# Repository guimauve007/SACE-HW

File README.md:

# SACE-HW
Répertoire contenant 2 cartes pour machine SACE:

## Getting started
- Installer la dernière version de KiCad ici: https://www.kicad.org/download/
- Cloner ce répertoire sur votre ordinateur local:

```
git clone https://github.com/guimauve007/SACE-HW.git
```

## carte_controle (V1)
Module de contrôle versatile avec les fonctionnalités suivantes:
- 2 connecteurs BNC pour lecture de tension & de courant des électrodes (à l'oscilloscope)
- 8 GPIO/ADC 12 bits 5V
- 2 sorties 0-5V analog (DAC)
- 2 sorties 0-10V analog (DAC)
- 8 sorties 5V haute vitesse (pour stepper drive)
- 2 relais NO 125VAC-10Amp
- 4 Mosfet Open Drain pour load 12V 5.7Amp Max
- Lecture de tension + courant des électrodes jusqu'à 200kSPS avec résolution 12 bits
- Possibilité d'enregistrer un log de données via carte SD
- Interface web utilisateur avec communication MQTT via ESP32
- Connecteurs I2C (x2) pour accessoires auxiliaires  

## interface_piezzos (V1)
- Amplificateur de signal via OP-Amp en mode comparateur (sortie 0-5V)

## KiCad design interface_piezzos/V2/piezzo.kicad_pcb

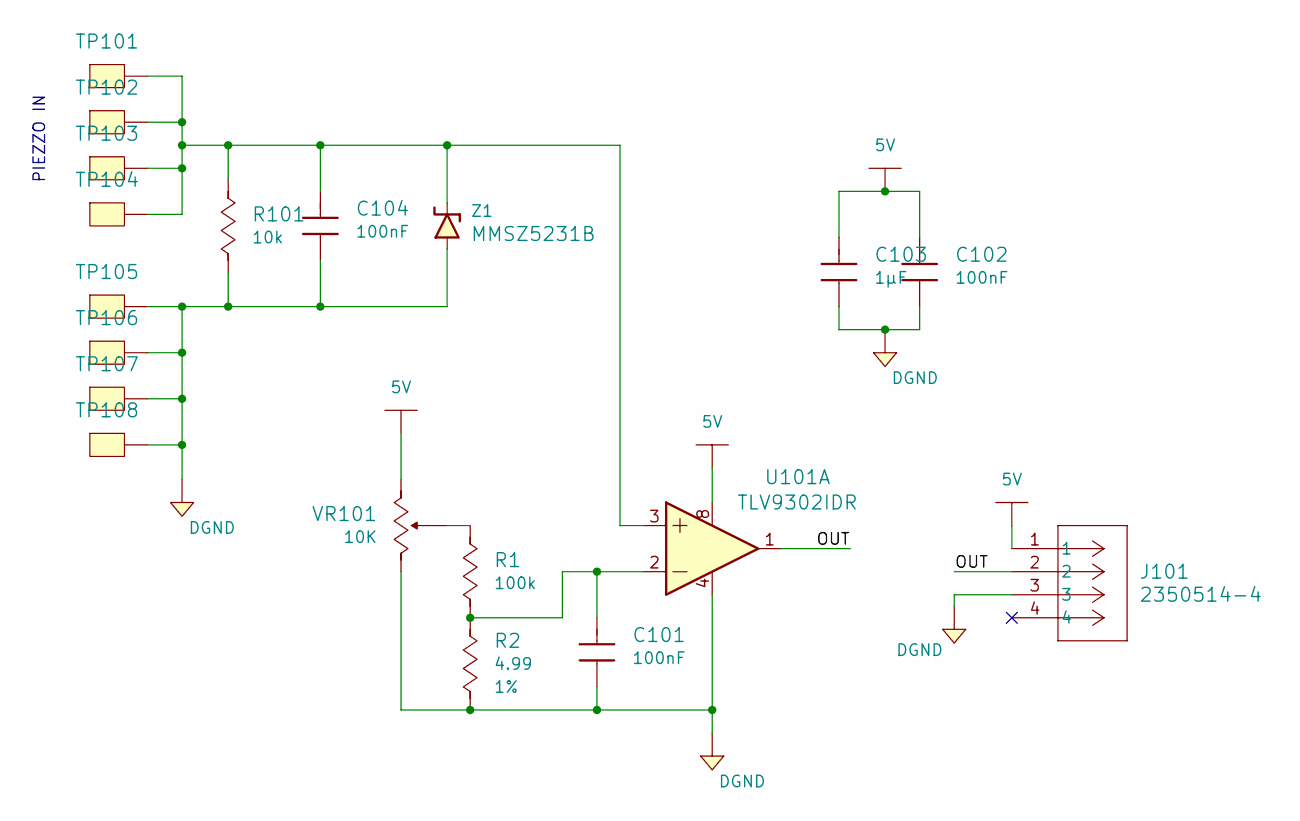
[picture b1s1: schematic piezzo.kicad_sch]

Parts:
C101, C102, C104: 885012207098; C0805; Tolerance (%) ±10%; Voltage Rated (Volt) 50V; Manufacturer Part Number 885012207098
C103: 885012107015; C0805; Tolerance (%) ±20%; Voltage Rated (Volt) 25V; Manufacturer Part Number 885012107015
J101: 2350514-4; CONN4_1155650000_TEC; Manufacturer Part Number 2350514-4
R1: RC0805FR-07100KL; R0805; Tolerance (%) ±1%; Manufacturer Part Number RC0805FR-07100KL
R2: RMCF0805FT4R99; R0805; Tolerance (%) 1%; Manufacturer Part Number RMCF0805FT4R99
R101: RC0805JR-0710KL; R0805; Tolerance (%) ±5%; Manufacturer Part Number RC0805JR-0710KL
TP101, TP102, TP103, TP104, TP105, TP106, TP107, TP108: Test_Point_THM; Keystone_5001; Manufacturer Part Number 5001
U101: TLV9302IDR; IC8_TLV9302IDR_TEX; Manufacturer Part Number TLV9302IDR
VR101: 67WR10KLF; 67W; Tolerance (%) ±10%; Manufacturer Part Number 67WR10KLF
Z1: MMSZ5231B; SOD-123FL; Manufacturer Part Number MMSZ5231B-7-F

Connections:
5V: C102.2, C103.2, J101.1, U101.8, VR101.3
/OUT: J101.2, U101.1
DGND: C101.1, C102.1, C103.1, C104.1, J101.3, R2.1, R101.1, TP105.1 (TP), TP106.1 (TP), TP107.1 (TP), TP108.1 (TP), U101.4, VR101.1, Z1.2 (Anode)
unnamed: C101.2, R1.1, R2.2, U101.2
unnamed: R1.2, VR101.2
unnamed: C104.2, R101.2, TP101.1 (TP), TP102.1 (TP), TP103.1 (TP), TP104.1 (TP), U101.3, Z1.1 (Cathode)

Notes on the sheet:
PIEZZO IN

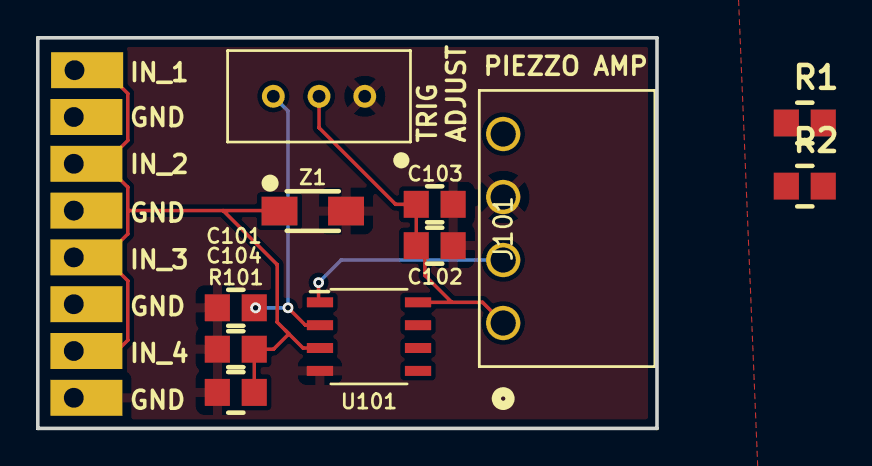
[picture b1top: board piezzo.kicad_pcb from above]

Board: 2 copper layers, 34.4 x 21.7 mm, 19 parts (0 on the bottom side), 6 nets.

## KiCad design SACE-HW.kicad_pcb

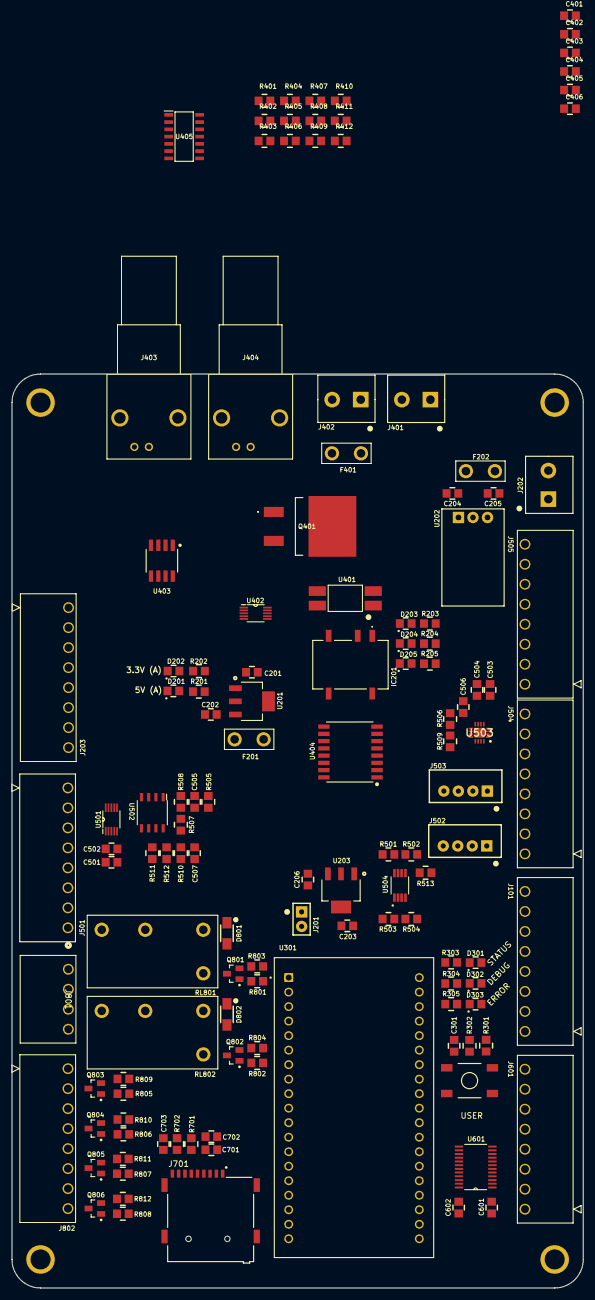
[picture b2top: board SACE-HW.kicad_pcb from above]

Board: 2 copper layers, 100.0 x 160.0 mm, 133 parts (0 on the bottom side), 115 nets, no tracks yet.

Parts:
C201, C203: 885012107005; C0805
C202, C206: 885012107014; C0805
C204, C205: 885012107018; C0805
C301, C401, C403, C405, C601, C602, C702, C703: 885012207098; C0805
C402, C404, C406: 885012207103; C0805
C501, C502, C503, C504, C505, C506, C507, C701: 885012107015; C0805
D201, D202, D203, D204, D205, D301: 150080VS75000; LED_0805_GREEN
D302: 150080YS75000; LED_0805_YELLOW
D303: 150080RS75000; LED_0805_RED
D801, D802: DSS16U; SOD-123FL
F201, F202: 39511000440; TE5_395
F401: 0698Q6300-01; TE5_395
H101, H102, H103, H104: Mounting-Hole-M3; Mounting_Hole_3mm
IC201: 1769205241
J101, J203, J501, J504, J505, J601, J802: 2350514-8; CONN8_2350514-8_TEC
J201: Header_Male_Pin_2.54mm_1X2_,_Unshrouded; Headers_2.54mm_1X2
J202, J401, J402: 1935161
J403, J404: RF1-01K-D-00-50-BK-HDW; RF101KD0050
J502, J503: XH-4A connector; XH-4A
J701: MEM2075-00-140-01-A; GCT_MEM2075-00-140-01-A
J801: 2350514-4; CONN4_1155650000_TEC
Q401: MCB90N12A-TP; MCB90N12ATP
Q801, Q802, Q803, Q804, Q805, Q806: PMV20XNER; SOT-23-3
R201, R204, R404: RC0805FR-075K6L; R0805
R202, R205, R303, R304, R305, R403, R505, R510: RC0805JR-072K2L; R0805
R203: RC0805JR-0733KL; R0805
R301, R501, R502, R503, R504: RC0805JR-074K7L; R0805
R302, R702: RC0805JR-07150RL; R0805
R401, R406, R407, R409, R411, R507, R508, R511, R512, R513, R803, R804, R809, R810, R811, R812: RC0805JR-0710KL; R0805
R402, R801, R802, R805, R806, R807, R808: RC0805JR-07330RL; R0805
R405, R410: ERJ-6ENF1404V; R0805
R408, R412, R701: RC0805FR-0747KL; R0805
R506, R509: 0hms_0.5W; R0805
RL801, RL802: ALQ312
SW301: PTS645SM43SMTR92; PTS645_6X6X4_SMD
U201, U203: AZ1117IH-3.3TRG1; SOT-223-3
U202: OKI-78SR-5_1.5-W36H-C; OKI-78SR_Horizontal
U301: ESP32-DEVKITC-32D; MODULE_ESP32-DEVKITC-32D
U401: LTV-816S; 4-SMD
U402: ADC124S021CIMM; SOP50P490X110-10N
U403: TMCS1101A3UQDT; SOIC-8
U404: ISO7341CQDWQ1; SOIC-16-wide
U405: MCP6L04T-E/SL; SOIC127P600X175-14N
U501: MCP4728T-E_UN; SOP50P490X110-10N
U502: TLV9302IDR; IC8_TLV9302IDR_TEX
U503: TLA2528IRTER; QFN50P300X300X80-17N-D
U504: TCA9617BDGKR; SOP65P490X110-8N
U601: 74LVC4245APW_118; SOP65P640X110-24N

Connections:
3.3VA: C201.2, R202.2, U201.2 (Vout), U201.4 (Vout_(TAB))
3.3VB: C203.2, C602.2, J201.1, R205.2, U203.2 (Vout), U203.4 (Vout_(TAB)), U601.23 (VCCB), U601.24 (VCCB_2)
5VA: C202.2, C401.2, C402.2, C403.2, C404.2, C405.2, C406.2, F201.2, R201.2, R401.1, U201.3 (Vin), U401.4 (C), U402.2 (VA), U403.8 (VS), U404.16 (BVDD), U405.4
5VB: C205.2, C206.2, C501.2, C502.2, C503.2, C504.2, C601.2, J203.3, J203.4, J502.4, J503.4, R204.2, R501.2, R502.2, R513.1, U202.3 (Vout), U203.3 (Vin), U501.1 (VDD), U503.7 (AVDD), U503.10 (DVDD), U504.8 (VCCB), U601.1 (VCCA)
12VB: C204.2, D801.1 (Cathode), D802.1 (Cathode), F202.2, IC201.2 (+VIN), J203.1, J203.2, J802.1, J802.3, J802.5, J802.7, R203.2, RL801.2, RL802.2, U202.1 (Vin), U502.8
/HV/CS_A: R401.2, U402.1 (~CS), U404.13 (B2)
/HV/HV_Sense: R405.1, R408.2, U402.5 (IN3), U405.3
/HV/MISO_A: U402.9 (DOUT), U404.11 (B4)
/HV/MOSI_A: U402.8 (DIN), U404.12 (B3)
/HV/SCL_5VK_A: U402.10 (SCLK), U404.14 (B1)
/HV/V_amp: J403.1, R409.2, U402.6 (IN2), U405.8
/HV/current_sense: J404.1, U402.7 (IN1), U403.7 (VOUT)
/HV/e-: F401.2, J402.1, R410.2
/I2C/GPIO0: J504.1, U503.15 (AIN0/GPIO0)
/I2C/GPIO1: J504.3, U503.16 (AIN1/GPIO1)
/I2C/GPIO2: J504.5, U503.1 (AIN2/GPIO2)
/I2C/GPIO3: J504.7, U503.2 (AIN3/GPIO3)
/I2C/GPIO4: J505.1, U503.3 (AIN4/GPIO4)
/I2C/GPIO5: J505.3, U503.4 (AIN5/GPIO5)
/I2C/GPIO6: J505.5, U503.5 (AIN6/GPIO6)
/I2C/GPIO7: J505.7, U503.6 (AIN7/GPIO7)
/I2C/OUTA: U501.6 (VOUTA), U502.3
/I2C/OUTA_10V: C505.2, J501.1, R505.2, R508.2, U502.1
/I2C/OUTB: U501.7 (VOUTB), U502.5
/I2C/OUTB_10V: C507.2, J501.3, R510.2, R512.2, U502.7
/I2C/OUTC: J501.5, U501.8 (VOUTC)
/I2C/OUTD: J501.7, U501.9 (VOUTD)
/I2C/SCL: R503.1, U504.2 (SCLA)
/I2C/SDA: R504.1, U504.3 (SDAA)
/I2C/decap: C506.2, R506.1, U503.8 (DECAP)
/IO0: J101.1, U301.J3-14 (IO0)
/IO1: J101.3, U301.J3-4 (IO1)
/IO4: U301.J3-13 (IO4), U601.21 (B0)
/IO5: U301.J3-10 (IO5), U601.20 (B1)
/IO6: U301.J3-19 (IO6), U601.19 (B2)
/IO7: U301.J3-18 (IO7), U601.18 (B3)
/IO8: U301.J3-17 (IO8), U601.17 (B4)
/IO9: U301.J2-16 (IO9), U601.16 (B5)
/IO10: U301.J2-17 (IO10), U601.15 (B6)
/IO11: U301.J2-18 (IO11), U601.14 (B7)
/IO12: J701.P7 (DAT0), U301.J2-13 (IO12), U404.6 (A4)
/IO13: J701.P3 (CMD), U301.J2-15 (IO13), U404.5 (A3)
/IO14: J701.P5 (CLK), U301.J2-12 (IO14), U404.3 (A1)
/IO15: U301.J3-16 (IO15), U404.4 (A2)
/IO16: R805.1, R809.2, U301.J3-12 (IO16)
/IO17: R806.1, R810.2, U301.J3-11 (IO17)
/IO18: R807.1, R811.2, U301.J3-9 (IO18)
/IO19: R808.1, R812.2, U301.J3-8 (IO19)
/IO21: J502.2, J503.2, R502.1, U301.J3-6 (IO21), U501.3 (SDA), U503.14 (SDA), U504.6 (SDAB)
/IO22: J502.3, J503.3, R501.1, U301.J3-3 (IO22), U501.2 (SCL), U503.13 (SCL), U504.7 (SCLB)
/IO23: J701.P2 (CD/DAT3), U301.J3-2 (IO23)
/IO32: J101.5, U301.J2-7 (IO32)
/IO33: J101.7, U301.J2-8 (IO33)
/IO34: C703.1, R701.1, R702.2, U301.J2-5 (IO34)
/IO35: R801.1, R803.2, U301.J2-6 (IO35)
/IO36: R802.1, R804.2, U301.J2-3 (IO36)
/IO39: U301.J2-4 (IO39), U401.1 (Anode)
/MCU/IO2: D301.2 (Anode), U301.J3-15 (IO2)
/MCU/IO3: D302.2 (Anode), U301.J3-5 (IO3)
/MCU/IO25: D303.2 (Anode), U301.J2-9 (IO25)
/MCU/IO26: C301.1, R302.1, U301.J2-10 (IO26)
/POWER_CTRL/OD1: J802.2, Q803.3 (D)
/POWER_CTRL/OD2: J802.4, Q804.3 (D)
/POWER_CTRL/OD3: J802.6, Q805.3 (D)
/POWER_CTRL/OD4: J802.8, Q806.3 (D)
/POWER_CTRL/RL1_NO_1: J801.1, RL801.3
/POWER_CTRL/RL1_NO_2: J801.2, RL801.4
/POWER_CTRL/RL2_NO_1: J801.3, RL802.3
/POWER_CTRL/RL2_NO_2: J801.4, RL802.4
GNDA: C201.1, C202.1, C401.1, C402.1, C403.1, C404.1, C405.1, C406.1, D201.1 (Cathode), D202.1 (Cathode), IC201.4 (-VOUT), J401.1, J403.2, J403.MH, J404.2, J404.MH, R404.1, R406.1, R408.1, R412.1, U201.1 (GND), U402.3 (GND), U403.3 (IN-), U403.4 (IN-), U403.5 (GND), U404.9 (BGND), U404.15 (BGND), U405.11
GNDB: C203.1, C204.1, C205.1, C206.1, C301.2, C501.1, C502.1, C503.1, C504.1, C505.1, C506.1, C507.1, C601.1, C602.1, C701.1, C702.2, C703.2, D203.1 (Cathode), D204.1 (Cathode), D205.1 (Cathode), IC201.1 (-VIN), J101.2, J101.4, J101.6, J101.8, J202.1, J203.5, J203.6, J203.7, J203.8, J501.2, J501.4, J501.6, J501.8, J502.1, J503.1, J504.2, J504.4, J504.6, J504.8, J505.2, J505.4, J505.6, J505.8, J701.P6 (VSS), J701.SH1 (SHIELD), Q801.2 (S), Q802.2 (S), Q803.2 (S), Q804.2 (S), Q805.2 (S), Q806.2 (S), R303.1, R304.1, R305.1, R403.1, R505.1, R507.1, R509.2, R510.1, R511.1, R803.1, R804.1, R809.1, R810.1, R811.1, R812.1, SW301.3, U202.2 (GND), U203.1 (GND), U301.J2-14 (GND1), U301.J3-1 (GND3), U301.J3-7 (GND2), U404.2 (AGND), U404.8 (AGND), U501.10 (VSS), U502.4, U503.9 (GND), U503.17 (EP), U504.4 (GND), U601.2 (DIR), U601.11 (GND_2), U601.12 (GND), U601.13 (GND_3), U601.22 (~OE)
HV: J401.2, J402.2, R405.2
unnamed: D201.2 (Anode), R201.1
unnamed: D202.2 (Anode), R202.1
unnamed: D203.2 (Anode), R203.1
unnamed: D204.2 (Anode), R204.1
unnamed: D205.2 (Anode), R205.1
unnamed: D301.1 (Cathode), R303.2
unnamed: D302.1 (Cathode), R304.2
unnamed: D303.1 (Cathode), R305.2
unnamed: D801.2 (Anode), Q801.3 (D), RL801.1
unnamed: D802.2 (Anode), Q802.3 (D), RL802.1
unnamed: F202.1, J202.2
unnamed: F201.1, IC201.5 (+VOUT)
unnamed: J701.P9 (CD), R702.1
unnamed: F401.1, Q401.2 (D)
unnamed: Q401.1 (G), R402.2
unnamed: Q401.3 (S), U403.1 (IN+), U403.2 (IN+)
unnamed: Q801.1 (G), R801.2
unnamed: Q802.1 (G), R802.2
unnamed: Q803.1 (G), R805.2
unnamed: Q804.1 (G), R806.2
unnamed: Q805.1 (G), R807.2
unnamed: Q806.1 (G), R808.2
unnamed: R301.1, R302.2, SW301.2
unnamed: R406.2, R407.2, U405.10
unnamed: R407.1, U405.1, U405.2
unnamed: R409.1, R411.2, U405.9
unnamed: R410.1, R412.2, U405.5
unnamed: R411.1, U405.6, U405.7
unnamed: R507.2, R508.1, U502.2
unnamed: R511.2, R512.1, U502.6
unnamed: R403.2, U401.2 (Cathode)
unnamed: R402.1, R404.2, U401.3 (E)
unnamed: R506.2, R509.1, U503.11 (ADDR)
unnamed: R513.2, U504.5 (EN)
unnamed: J601.1, U601.3 (A0)
unnamed: J601.2, U601.4 (A1)
unnamed: J601.3, U601.5 (A2)
unnamed: J601.4, U601.6 (A3)
unnamed: J601.5, U601.7 (A4)
unnamed: J601.6, U601.8 (A5)
unnamed: J601.7, U601.9 (A6)
unnamed: J601.8, U601.10 (A7)
VDD: C701.2, C702.1, J201.2, J701.P4 (VDD), R301.2, R503.2, R504.2, R701.2, U301.J2-1 (3V3), U301.J2-2 (EN), U404.1 (AVDD), U504.1 (VCCA)

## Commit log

2024-05-13 nouveau projet + ajout gitignore
2024-05-13 repo cleanup + modif gitignore
2024-05-16 update schematic
2024-05-28 modif schématique
2024-05-29 update schematique
2024-06-03 finalisation de la schématique
2024-06-20 clean up
2024-07-05 parts placement finished
2024-07-09 gerber + commande JLC
2024-08-14 un peu d'ordre la dedans
2024-09-09 ajout gitignore + versions
